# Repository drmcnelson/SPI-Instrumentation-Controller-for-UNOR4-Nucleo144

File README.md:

# SPI-Instrumentation-Controller-for-UNOR4-Nucleo144

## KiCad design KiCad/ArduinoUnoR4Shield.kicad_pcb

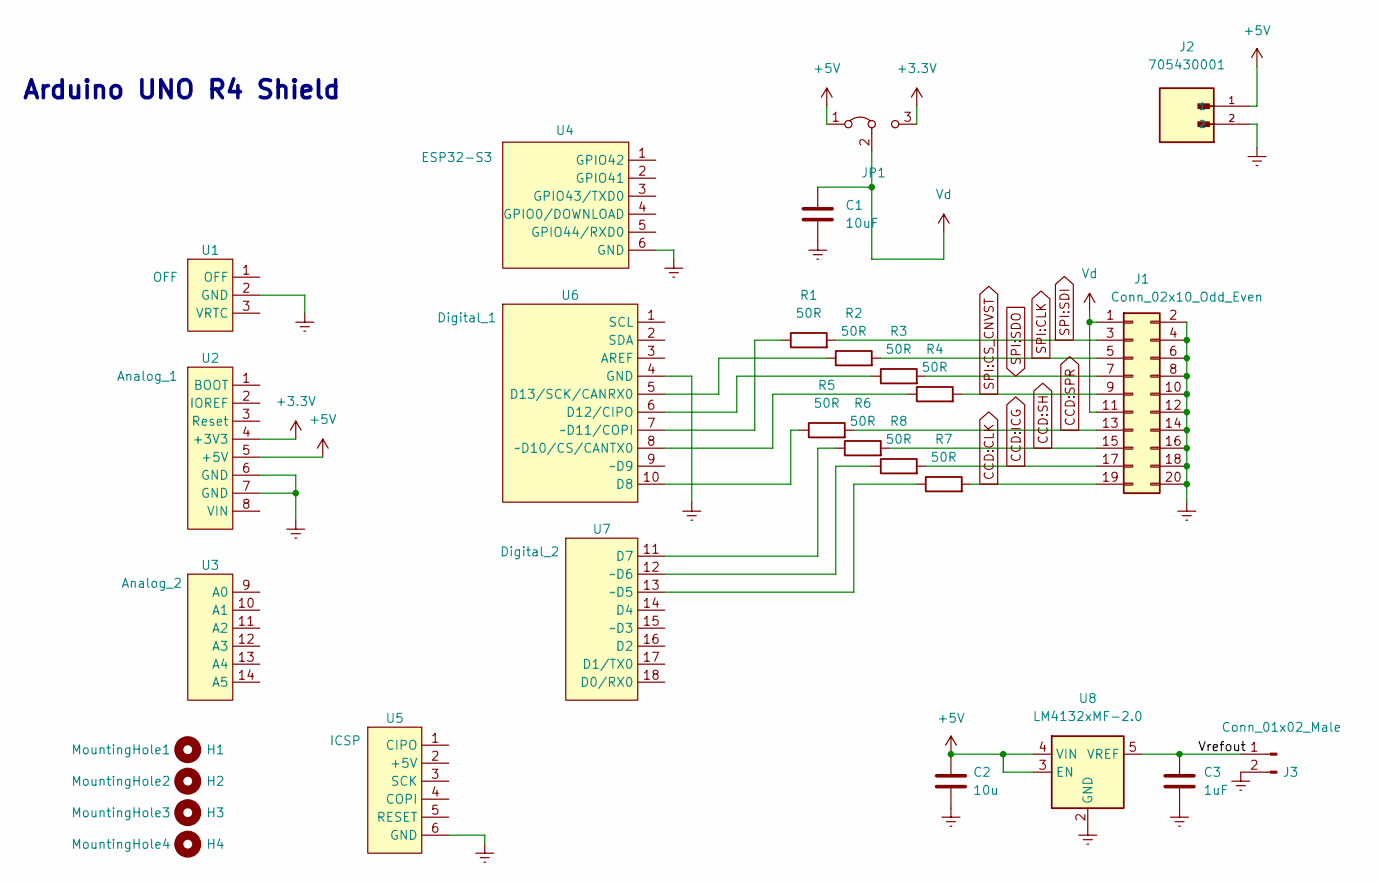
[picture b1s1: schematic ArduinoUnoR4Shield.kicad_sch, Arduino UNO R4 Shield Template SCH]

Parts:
C1: 10uF; C_1206_3216Metric
C2: 10u; C_0603_1608Metric_Pad1.08x0.95mm_HandSolder; Digikey 490-12317-1-ND
C3: 1uF; C_0603_1608Metric_Pad1.08x0.95mm_HandSolder; Digikey 1276-1034-1-ND
H1: MountingHole1; Arduino_MountingHole
H2: MountingHole2; Arduino_MountingHole
H3: MountingHole3; Arduino_MountingHole
H4: MountingHole4; Arduino_MountingHole
J1: Conn_02x10_Odd_Even; PinHeader_2x10_P2.54mm_Vertical; Digikey 3M156308-20-ND
J2: 705430001; MOLEX_705430001; PARTREV M1; Digikey WM4800-ND
J3: Conn_01x02_Male; PinHeader_1x02_P2.54mm_Vertical; Digikey 3M156268-02-ND
JP1: Conn_01x03_Male; PinHeader_1x03_P2.54mm_Vertical; Manufacturer_Part_Number GRPB031VWVN-RC
R1, R2, R3, R4, R5, R6, R7, R8: 50R; R_0805_2012Metric_Pad1.20x1.40mm_HandSolder
U1: OFF; Arduino_PinSocket_1x03_P2.54mm_Vertical
U2: Analog_1; Arduino_PinSocket_1x08_P2.54mm_Vertical
U3: Analog_2; Arduino_PinSocket_1x06_P2.54mm_Vertical
U4: ESP32-S3; Arduino_PinSocket_2x03_P2.54mm_Vertical
U5: ICSP; Arduino_PinSocket_2x03_P2.54mm_Vertical
U6: Digital_1; Arduino_PinSocket_1x10_P2.54mm_Vertical
U7: Digital_2; Arduino_PinSocket_1x08_P2.54mm_Vertical
U8: LM4132xMF-2.0; SOT-23-5; Digikey LM4132BMF-2.0/NOPBCT-ND

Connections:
+3.3V: JP1.3 (B), U2.4 (+3V3)
+5V: C2.1, J2.1, JP1.1 (A), U2.5 (+5V), U8.3 (EN), U8.4 (VIN)
/Vrefout: C3.1, J3.1, U8.5 (VREF)
CCD:CLK: J1.19, R7.2
CCD:ICG: J1.17, R8.2
CCD:SH: J1.15, R6.2
CCD:SPR: J1.13, R5.2
Earth: C1.2, C2.2, C3.2, J1.2, J1.4, J1.6, J1.8, J1.10, J1.12, J1.14, J1.16, J1.18, J1.20, J2.2, J3.2, U1.2 (GND), U2.6 (GND), U2.7 (GND), U4.6 (GND), U5.6 (GND), U6.4 (GND), U8.2 (GND)
unnamed: R5.1, U6.10 (D8)
unnamed: R3.1, U6.6 (D12/CIPO)
unnamed: R2.1, U6.5 (D13/SCK/CANRX0)
unnamed: R4.1, U6.8 (~D10/CS/CANTX0)
unnamed: R1.1, U6.7 (~D11/COPI)
unnamed: R6.1, U7.11 (D7)
unnamed: R7.1, U7.13 (~D5)
unnamed: R8.1, U7.12 (~D6)
SPI:CLK: J1.5, R2.2
SPI:CS_CNVST: J1.9, R4.2
SPI:SDI: J1.3, R1.2
SPI:SDO: J1.7, R3.2
Vd: C1.1, J1.1, J1.11, JP1.2 (C)

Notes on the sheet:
Arduino UNO R4 Shield

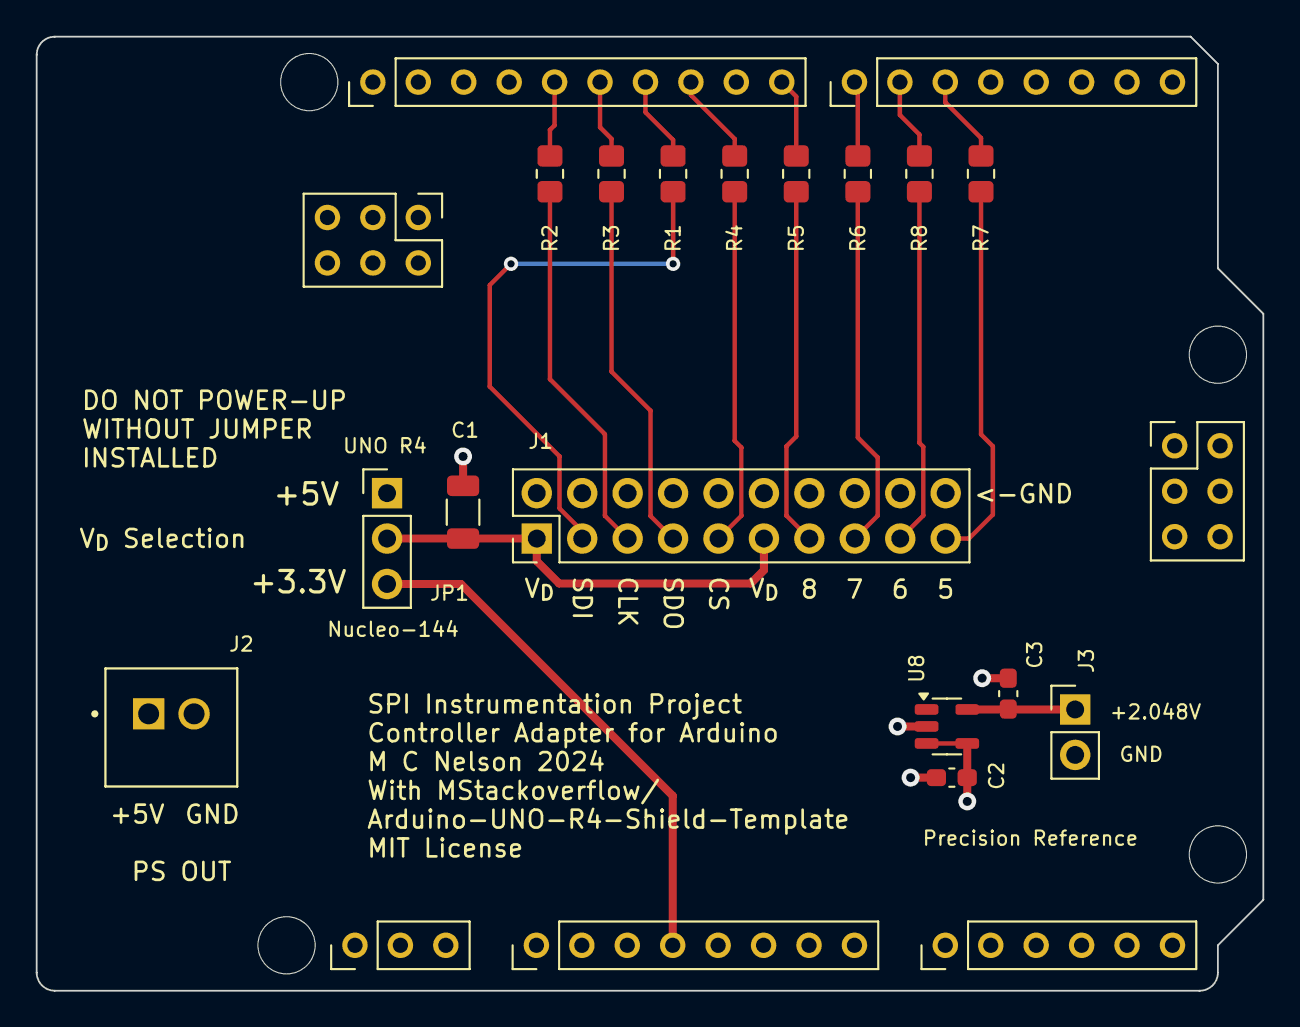
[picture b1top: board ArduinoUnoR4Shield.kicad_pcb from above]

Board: 4 copper layers, 68.6 x 53.3 mm, 27 parts (0 on the bottom side), 21 nets.

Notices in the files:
KiCad/ArduinoUnoR4Shield.kicad_pcb:
MIT License
